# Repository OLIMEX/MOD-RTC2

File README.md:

# MOD-RTC2
Extremly accurate RTC UEXT module to connect to Arduino and Linux boards

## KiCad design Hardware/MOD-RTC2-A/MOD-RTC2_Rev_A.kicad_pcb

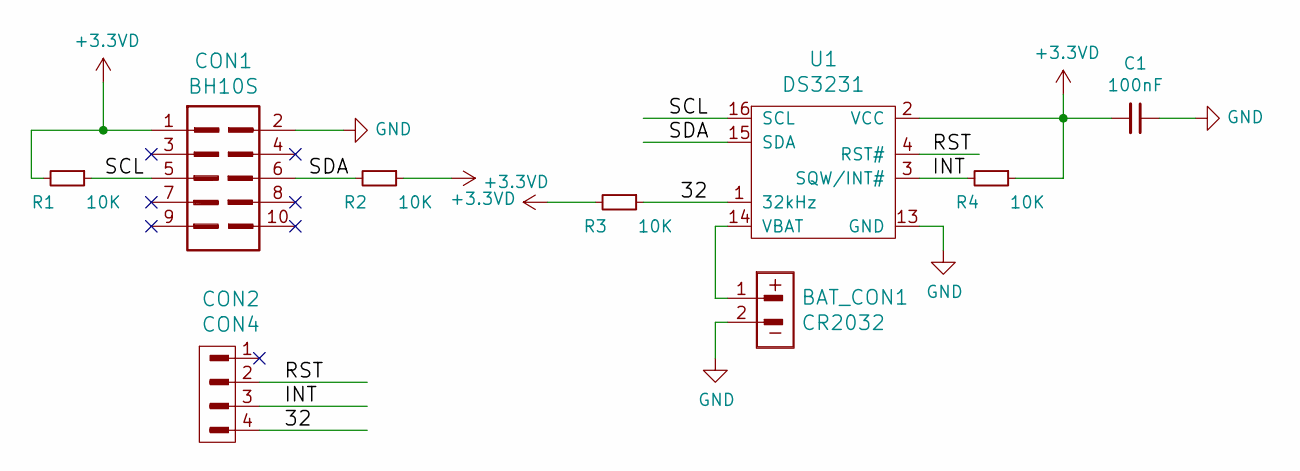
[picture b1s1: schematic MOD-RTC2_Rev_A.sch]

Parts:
BAT_CON1: CR2032; CR2032H_PTH
C1: 100nF; C_0603_5MIL_DWS
CON1: BH10S; UEXTF
CON2: CON4; HN1x4
R1, R2, R3, R4: 10K; R_0603_5MIL_DWS
U1: DS3231; SO-16

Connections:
+3.3VD: C1.2, CON1.1, R1.2, R2.1, R3.2, R4.1, U1.2 (VCC)
/32: CON2.4, R3.1, U1.1 (32kHz)
/INT: CON2.3, R4.2, U1.3 (SQW/INT#)
/RST: CON2.2, U1.4 (RST#)
/SCL: CON1.5, R1.1, U1.16 (SCL)
/SDA: CON1.6, R2.2, U1.15 (SDA)
GND: BAT_CON1.2, C1.1, CON1.2, U1.5 (GND), U1.6 (GND), U1.7 (GND), U1.8 (GND), U1.9 (GND), U1.10 (GND), U1.11 (GND), U1.12 (GND), U1.13 (GND)
unnamed: BAT_CON1.1, U1.14 (VBAT)

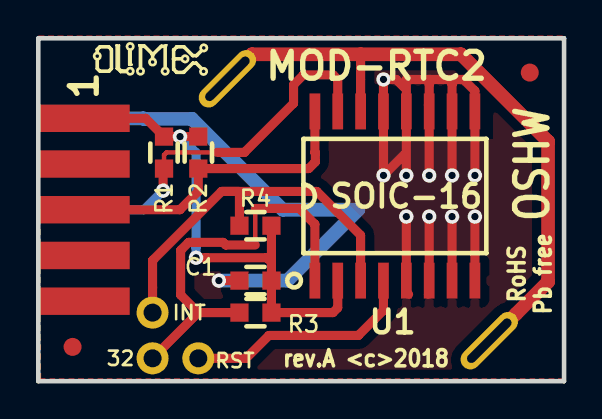
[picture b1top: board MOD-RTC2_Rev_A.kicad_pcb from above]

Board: 2 copper layers, 29.2 x 19.1 mm, 11 parts (1 on the bottom side), 8 nets.

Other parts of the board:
Ref*: Val**; Fiducial1x3_transp
Ref*#2: Val**; Fiducial1x3_transp

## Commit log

2018-05-17 upload initial hardware and software files
